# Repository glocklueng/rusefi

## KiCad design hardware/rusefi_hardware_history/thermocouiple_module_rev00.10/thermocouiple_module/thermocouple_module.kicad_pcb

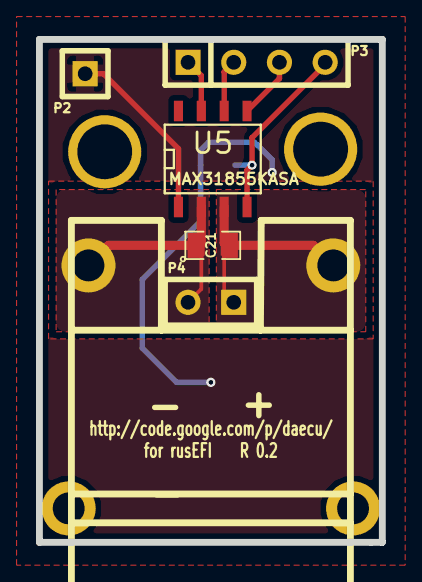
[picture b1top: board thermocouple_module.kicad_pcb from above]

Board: 2 copper layers, 19.0 x 27.9 mm, 9 parts (1 on the bottom side), 7 nets.

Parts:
C8: 100nF; SM0805-SM0603
C21: 10nF; SM0805-SM0603
P1: CONN_2; tcpl_PCC-SMP
P2: CONN_1; SIL-1
P3: CONN_4; SIL-4
P4: CONN_2; SIL-2
U5: MAX31855KASA; SO8E
V801, V802: VIA; 1pin

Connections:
3.3v: C8.1, P3.4, U5.4
//CS: P3.2, U5.6
/MISO: P3.1, U5.7
/SCK: P3.3, U5.5
/TCPL+: C21.2, P1.2, P4.1, U5.3
/TCPL-: C21.1, P1.1, P4.2, U5.2
GND: C8.2, P2.1, U5.1

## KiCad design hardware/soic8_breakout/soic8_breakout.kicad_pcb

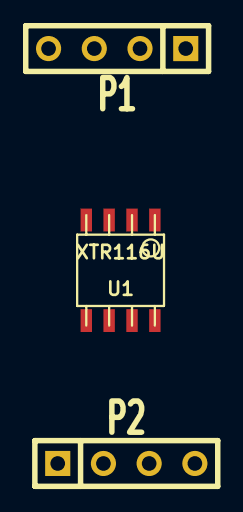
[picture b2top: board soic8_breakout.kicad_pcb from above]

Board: 2 copper layers, 3 parts (0 on the bottom side), 4 nets, no tracks yet.

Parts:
P1, P2: CONN_4; SIL-4
U1: XTR116U; so-8

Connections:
unnamed: P2.2, U1.6
unnamed: P1.3, U1.3
unnamed: P1.2, U1.2
unnamed: P1.1, U1.1

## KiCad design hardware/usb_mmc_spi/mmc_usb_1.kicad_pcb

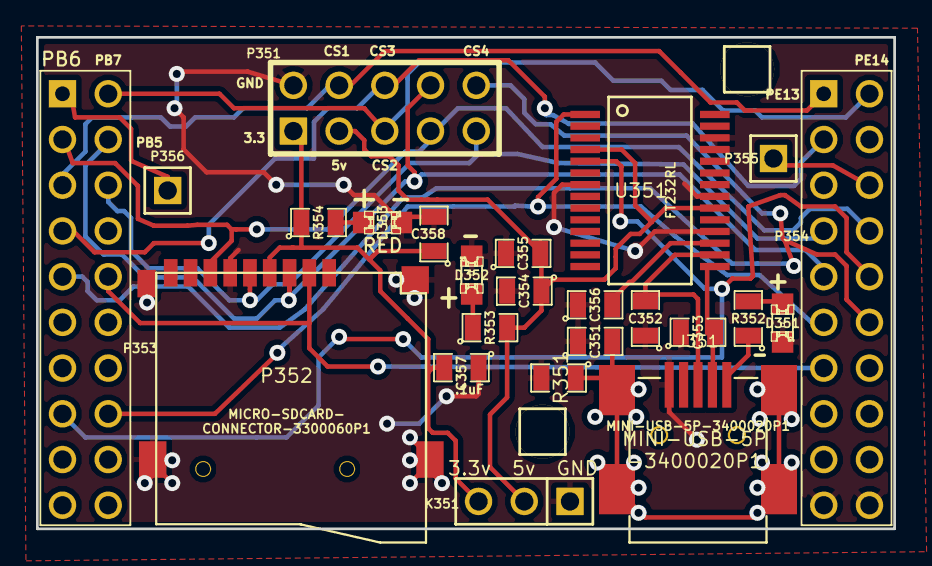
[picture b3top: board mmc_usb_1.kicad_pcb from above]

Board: 2 copper layers, 47.6 x 27.3 mm, 27 parts (1 on the bottom side), 23 nets.

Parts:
C351: 4700pF; SM0805
C352, C353: 47pF; SM0805
C354, C358: 4.7uF; SM0805
C355, C356, C357: .1uF; SM0805
D351: GREEN; LED-0805
D352, D353: RED; LED-0805
G305: LOGO; LOGO_F
J351: MINI-USB-5P-3400020P1
K351: CONN_3; PIN_ARRAY_3_A
M351, M352: CONN_1; PIN_ARRAY_1
P351: CONN_5X2; PIN_ARRAY_5x2
P352: MICRO-SDCARD-CONNECTOR-3300060P1
P353, P354: CONN_10X2; PIN_ARRAY_10X2
P355, P356: CONN_1; PIN_ARRAY_1
R351: 1M; SM0805
R352, R353, R354: 1k; SM0805
U351: FT232RL; ssop-28

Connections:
/3.3V: C357.2, C358.1, K351.3, P351.1, P352.4, R354.1
/5V: C354.1, C355.2, K351.2, P351.3, R353.2, U351.4, U351.20
/CAN_TX: P353.1, P356.1
/CS1: P351.4, P353.5, P354.1
/CS2: P351.5, P353.2, P354.2
/CS3: P351.6, P353.7, P354.3
/CS4: P351.10, P353.9, P354.12
/CS_SD_MODULE: P352.2, P353.10, P354.13
/SPI_MISO: P351.7, P352.7, P353.3, P354.8
/SPI_MOSI: P351.8, P352.3, P353.4, P354.9
/SPI_SCK: P351.9, P352.5, P353.6, P354.7
/USART_RX: P353.16, P354.11, U351.1
/USART_TX: P353.15, P354.10, U351.5
GND: C351.1, C352.1, C353.1, C354.2, C355.1, C356.1, C357.1, C358.2, D351.2, D352.2, D353.2, J351.5, K351.1, P351.2, P352.6, P352.G1, P352.G2, P352.G3, P352.G4, P354.19, P354.20, R351.2, U351.7, U351.18, U351.21, U351.25, U351.26
unnamed: J351.1, R352.1
unnamed: C351.2, J351.6, R351.1
unnamed: C353.2, J351.2, U351.15
unnamed: D351.1, R352.2
unnamed: P354.6, P355.1
unnamed: C356.2, U351.17
unnamed: D352.1, R353.1
unnamed: C352.2, J351.3, U351.16
unnamed: D353.1, R354.2

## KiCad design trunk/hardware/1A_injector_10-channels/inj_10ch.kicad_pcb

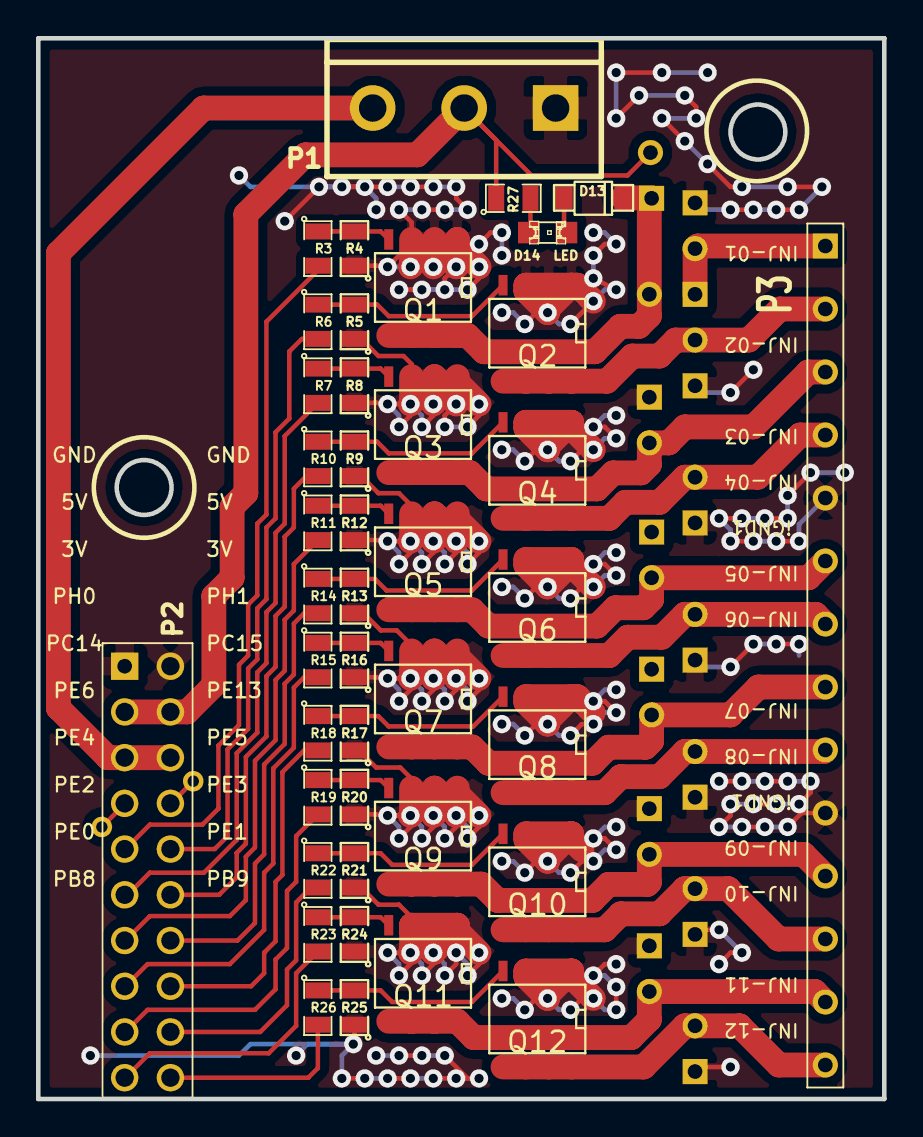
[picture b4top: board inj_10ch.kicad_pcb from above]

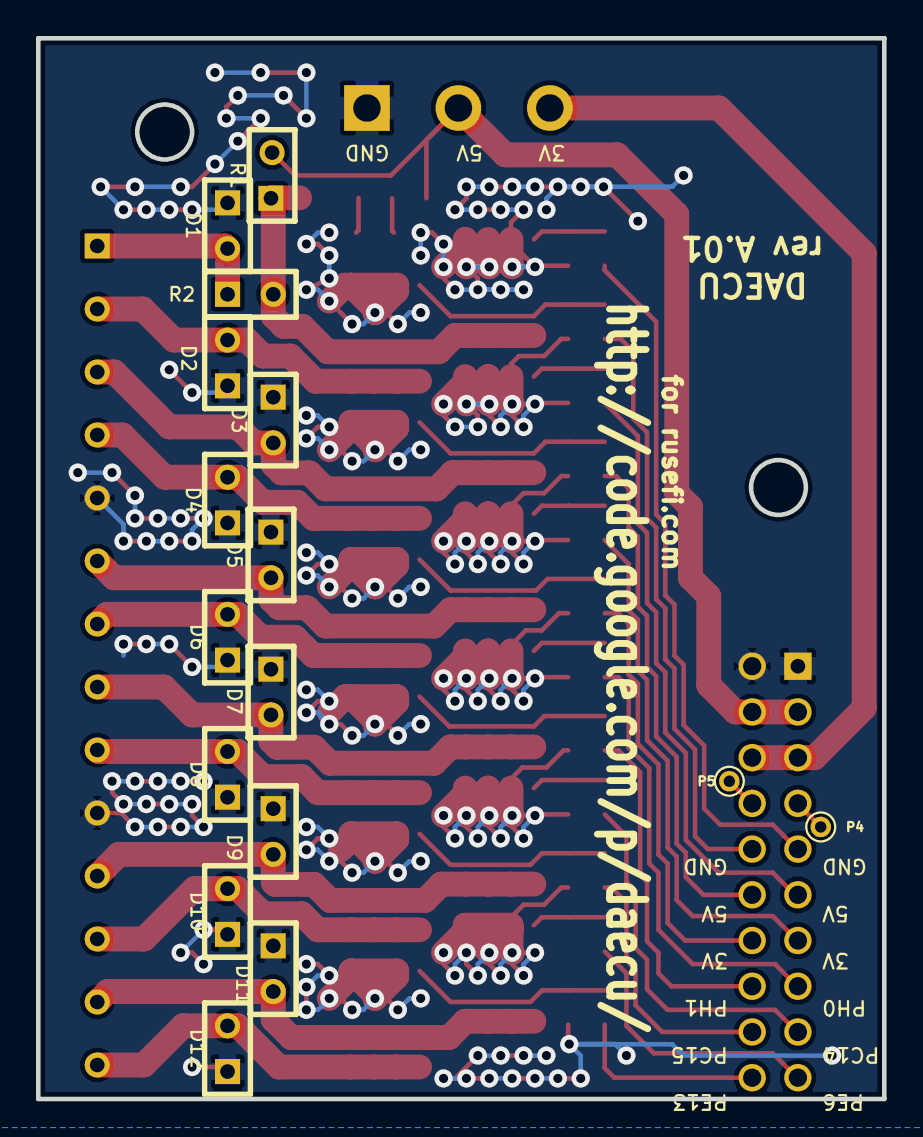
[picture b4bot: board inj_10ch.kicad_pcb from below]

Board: 2 copper layers, 47.0 x 58.9 mm, 58 parts (16 on the bottom side), 44 nets.

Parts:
D1, D2, D3, D4, D5, D6, D7, D8, D9, D10, D11, D12: DIODE; SIL-2
D13: DIODE; SOD-123
D14: LED; LED-0805
P1: CONN_3; bornier3
P2: CONN_10X2; pin_array_10x2
P3: CONN_14; SIL-14
P4, P5: CONN_1; PINTST
Q1, Q2, Q3, Q4, Q5, Q6, Q7, Q8, Q9, Q10, Q11, Q12: OVP_DRIVER; SO8E_ST
R1: OPT; SIL-2
R2: 0R; SIL-2
R3, R6, R7, R10, R11, R14, R15, R18, R19, R22, R23, R26: 20R; SM0805
R4, R5, R8, R9, R12, R13, R16, R17, R20, R21, R24, R25, R27: 1K; SM0805

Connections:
/3V: P1.3, P2.5, P2.6
/5V: P1.2, P2.3, P2.4, R1.2, R27.1
/INJ-01: D13.2, Q1.2, R1.1, R2.2
/INJ-01_2: D1.2, P3.1, R2.1
/INJ-01_5V: P2.9, R3.2
/INJ-02: D2.2, P3.2, Q2.2
/INJ-02_5V: P2.10, R6.2
/INJ-03: D3.2, P3.3, Q3.2
/INJ-03_5V: P2.11, R7.2
/INJ-04: D4.2, P3.4, Q4.2
/INJ-04_5V: P2.12, R10.2
/INJ-05: D5.2, P3.6, Q5.2
/INJ-05_5V: P2.13, R11.2
/INJ-06: D6.2, P3.7, Q6.2
/INJ-06_5V: P2.14, R14.2
/INJ-07: D7.2, P3.8, Q7.2
/INJ-07_5V: P2.15, R15.2
/INJ-08: D8.2, P3.9, Q8.2
/INJ-08_5V: P2.16, R18.2
/INJ-09: D9.2, P3.11, Q9.2
/INJ-09_5V: P2.17, R19.2
/INJ-10: D10.2, P3.12, Q10.2
/INJ-10_5V: P2.18, R22.2
/INJ-11: D11.2, P3.13, Q11.2
/INJ-11_5V: P2.19, R23.2
/INJ-12: D12.2, P3.14, Q12.2
/INJ-12_5V: P2.20, R26.2
/PH0: P2.7, P4.1
/PH1: P2.8, P5.1
GND: D1.1, D2.1, D3.1, D4.1, D5.1, D6.1, D7.1, D8.1, D9.1, D10.1, D11.1, D12.1, P1.1, P2.1, P2.2, P3.5, P3.10, Q1.3, Q2.3, Q3.3, Q4.3, Q5.3, Q6.3, Q7.3, Q8.3, Q9.3, Q10.3, Q11.3, Q12.3, R4.1, R5.1, R8.1, R9.1, R12.1, R13.1, R16.1, R17.1, R20.1, R21.1, R24.1, R25.1
unnamed: Q2.1, R5.2, R6.1
unnamed: Q1.1, R3.1, R4.2
unnamed: Q6.1, R13.2, R14.1
unnamed: Q11.1, R23.1, R24.2
unnamed: Q9.1, R19.1, R20.2
unnamed: Q4.1, R9.2, R10.1
unnamed: Q5.1, R11.1, R12.2
unnamed: Q3.1, R7.1, R8.2
unnamed: Q10.1, R21.2, R22.1
unnamed: Q8.1, R17.2, R18.1
unnamed: Q12.1, R25.2, R26.1
unnamed: D14.1, R27.2
unnamed: D13.1, D14.2
unnamed: Q7.1, R15.1, R16.2
